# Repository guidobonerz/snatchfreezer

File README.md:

# SnatchFreezer (Beta)
SnatchFreezer is a project for Highspeed photography

Runs on Windows, Mac and Linux

This project also contains all required software and PCB layouts including:
- JavaFX - Controller Frontend
- Arduino Sketch
- Eagle PCB

Current Features:
- Connect up to six 12V driven valves or similar devices directly with 5 timing entries each.
- Connect up to two camera and/or flashes.

- Load and Save your settings
- Test all channels separately or altogether for 100ms.
- Toggle flushing all or single siphons from UI.
- Set amount of cycle loops
- Set delay time after each cycle loop.
- Describe each channel and/or the whole project
- Presets for TaT and Crown
- View log protocol
- Minimum valve delay/release time combination: 0,015 s -> 15 ms -> 15000 us / 0,004 s -> 4 ms -> 4000 us

Known Bugs:
- Data transfer sometimes hangs

Future plans:
- WLAN and/or Bluetooth Module
- Rest Api
- Android Client

# Build Java Application
mvn jfx:jar

# Download latest Frontend
[Snathfreezer Frontend](https://github.com/guidobonerz/snatchfreezer/blob/develop/download/snatchfreezer.zip)

## Shot 1

## Shot 2

## Controller View

## PCB

## Frame

## Siphons

## Valves

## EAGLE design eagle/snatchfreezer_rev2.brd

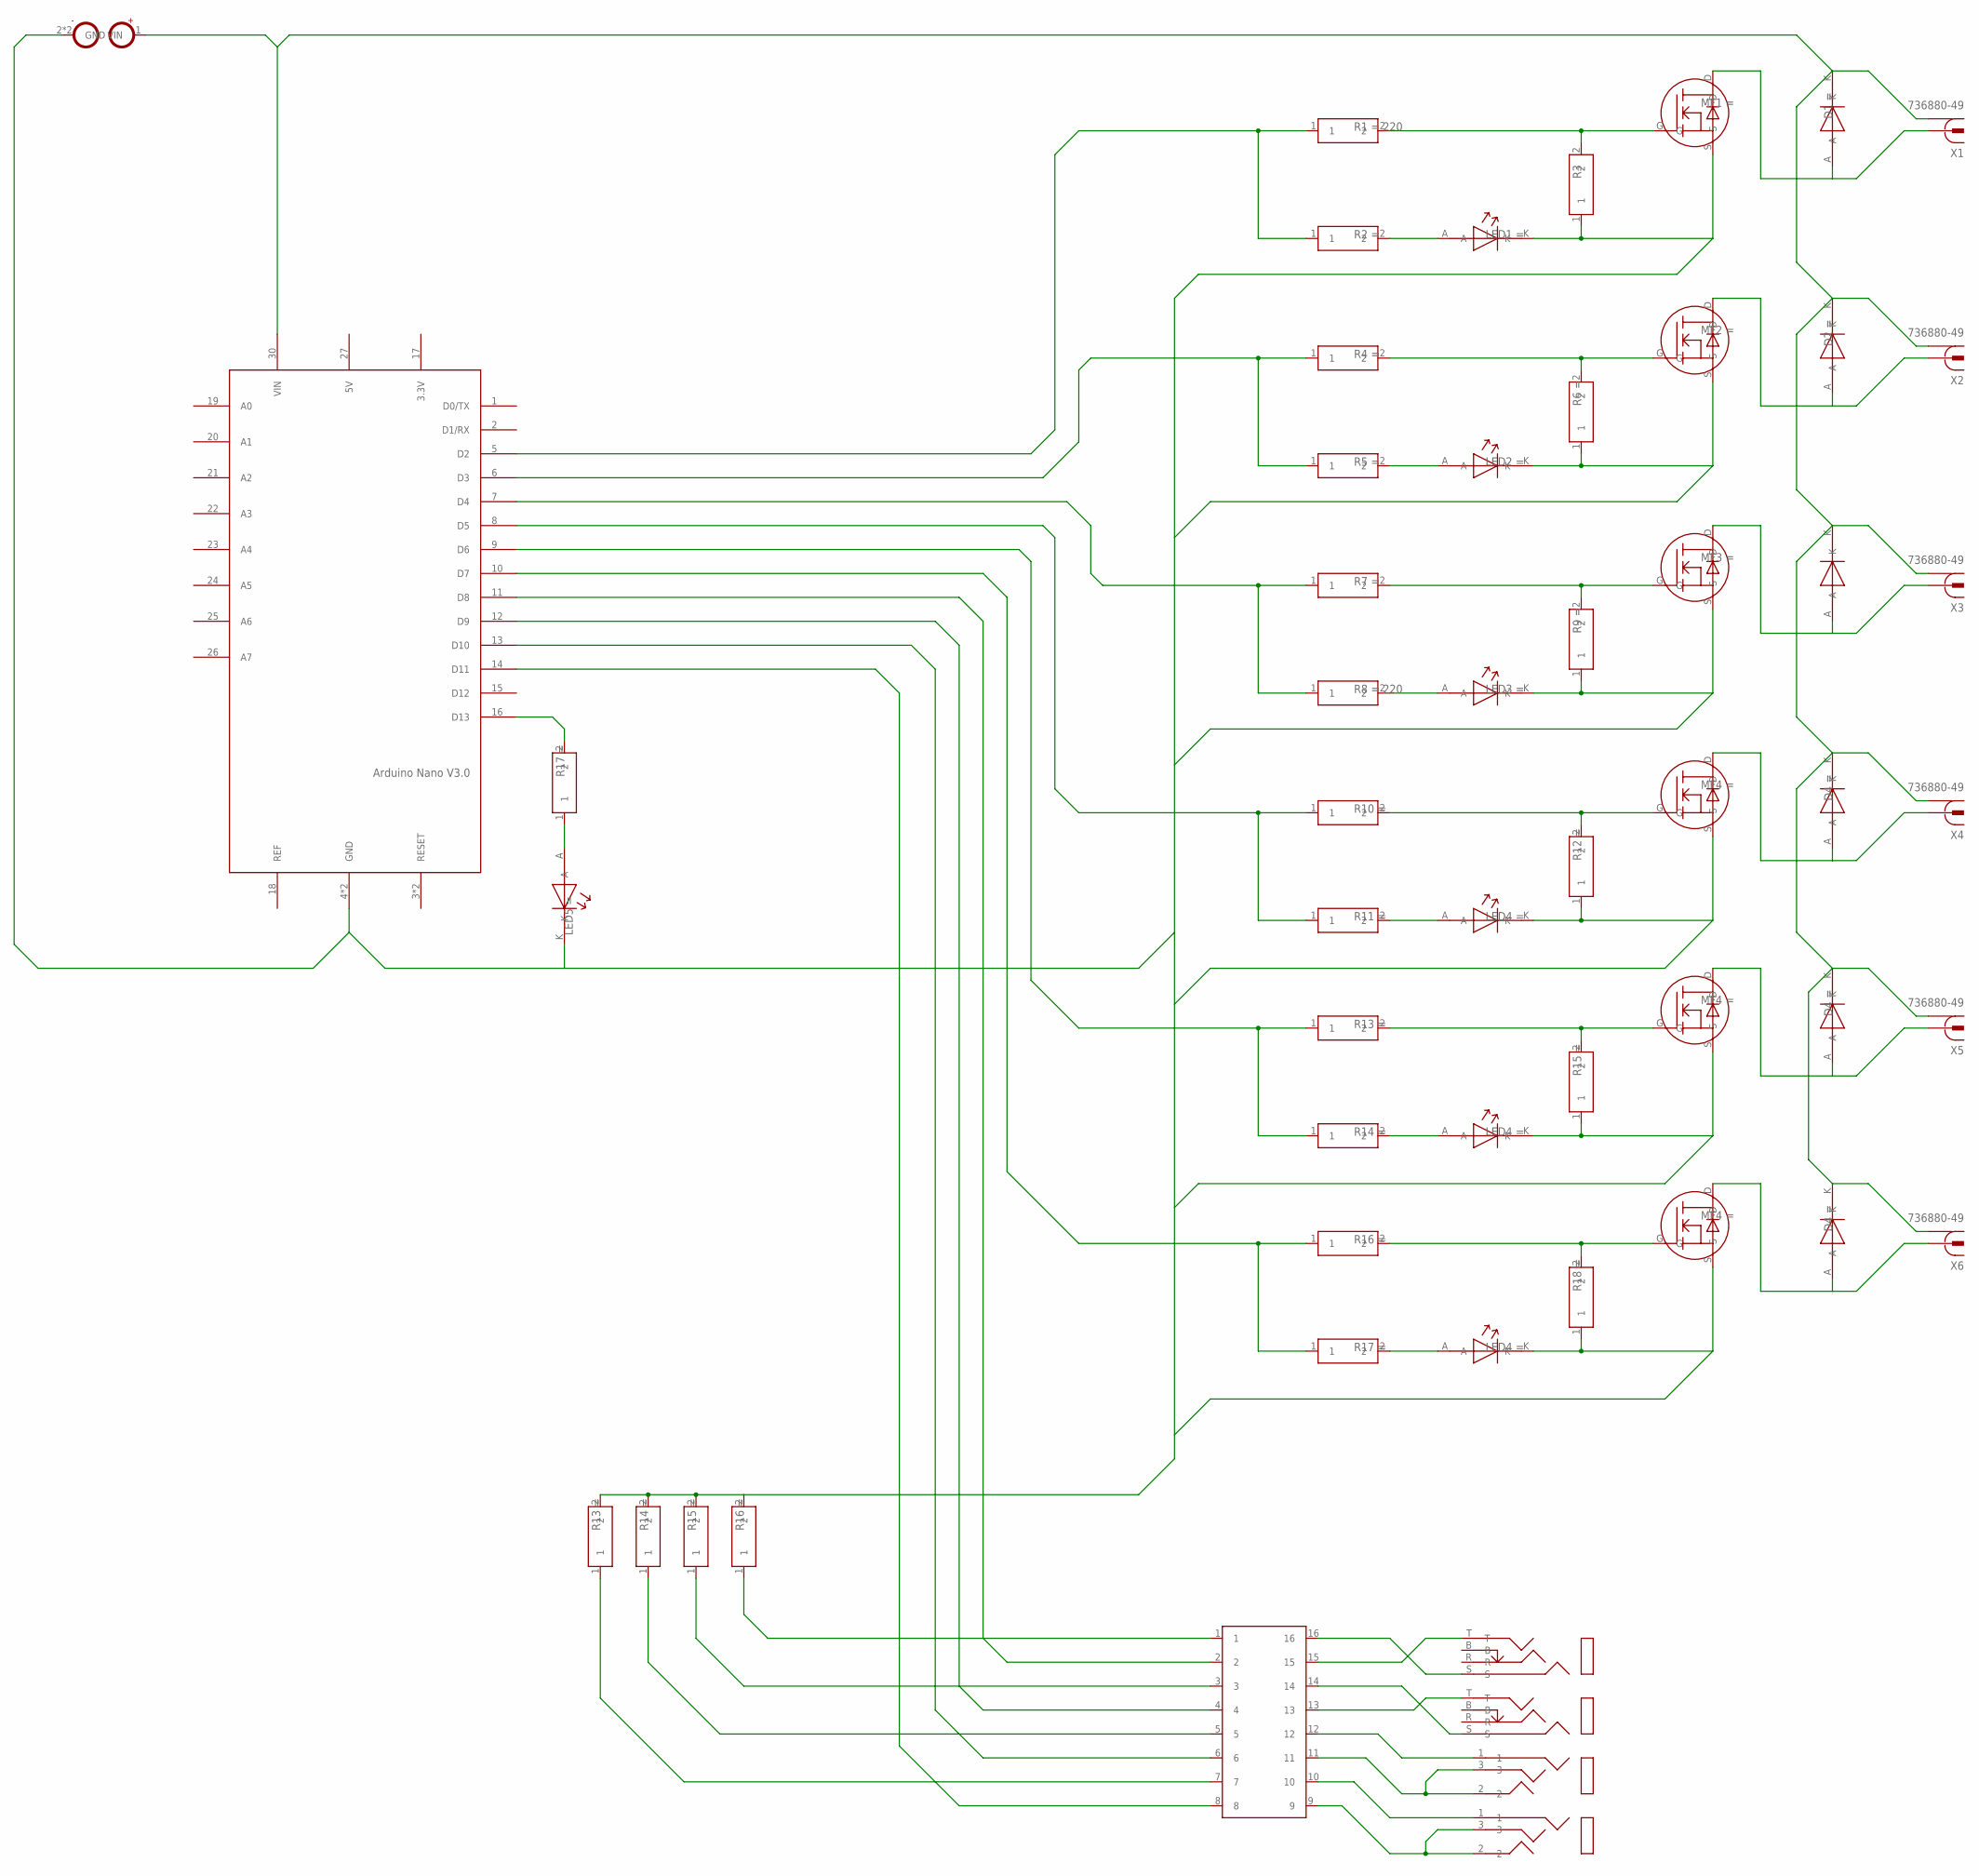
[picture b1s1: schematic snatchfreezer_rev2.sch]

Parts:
R1, R2, R3, R4, R5, R6, R7, R8, R9, R10, R11, R12, R13, R14, R15, R16, R17, R18: RESISTOR
U$1: ARDUINO_NANO30
U$2, U$3, U$4, U$16, U$20, U$28: IRLR8721
U$5, U$10, U$11, U$17, U$22, U$23, U$31: LED3MM
U$6, U$7: PHONEJACK_35
U$8: IC-16
U$9, U$30, U$37, U$38, U$39: RESISTOR
U$12, U$13, U$14, U$21, U$24, U$32: DIODE
U$36: POWER_CONNECT
U$40, U$41: PHONEJACK_25
X1, X2, X3, X4, X5, X6: 736880-49

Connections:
12V2: U$1.30 (VIN), U$12.K, U$13.K, U$14.K, U$21.K, U$24.K, U$32.K, U$36.1 (VIN), X1.GND (1), X2.GND (1), X3.GND (1), X4.GND (1), X5.GND (1), X6.GND (1)
GND2: R3.1, R6.1, R9.1, R12.1, R15.1, R18.1, U$1.4 (GND), U$1.29 (GND), U$2.S, U$3.S, U$4.S, U$5.K, U$10.K, U$11.K, U$16.S, U$17.K, U$20.S, U$22.K, U$23.K, U$28.S, U$30.2, U$31.K, U$36.2 (GND), U$36.3 (GND), U$37.2, U$38.2, U$39.2
unnamed: R1.2, R3.2, U$2.G
unnamed: U$2.D, U$12.A, X1.SIGNAL (2)
unnamed: R2.2, U$11.A
unnamed: U$7.S, U$8.16
unnamed: U$8.1, U$30.1
unnamed: R1.1, R2.1, U$1.5 (D2)
unnamed: U$3.D, U$13.A, X2.SIGNAL (2)
unnamed: U$8.3, U$37.1
unnamed: U$7.T, U$8.15
unnamed: R5.2, U$10.A
unnamed: R4.2, R6.2, U$3.G
unnamed: R4.1, R5.1, U$1.6 (D3)
unnamed: U$20.D, U$24.A, X3.SIGNAL (2)
unnamed: U$8.5, U$38.1
unnamed: U$8.7, U$39.1
unnamed: R8.2, U$23.A
unnamed: R7.2, R9.2, U$20.G
unnamed: R7.1, R8.1, U$1.7 (D4)
unnamed: U$28.D, U$32.A, X4.SIGNAL (2)
unnamed: U$1.11 (D8), U$8.2
unnamed: U$1.12 (D9), U$8.4
unnamed: R11.2, U$31.A
unnamed: R10.2, R12.2, U$28.G
unnamed: R10.1, R11.1, U$1.8 (D5)
unnamed: U$1.13 (D10), U$8.6
unnamed: U$1.14 (D11), U$8.8
unnamed: U$6.T, U$8.13
unnamed: U$6.S, U$8.14
unnamed: U$4.D, U$14.A, X5.SIGNAL (2)
unnamed: R14.2, U$5.A
unnamed: U$8.12, U$40.1
unnamed: U$8.11, U$40.2, U$40.3
unnamed: U$8.10, U$41.1
unnamed: U$8.9, U$41.2, U$41.3
unnamed: U$1.16 (D13), U$9.2
unnamed: U$9.1, U$22.A
unnamed: R13.2, R15.2, U$4.G
unnamed: R13.1, R14.1, U$1.9 (D6)
unnamed: U$16.D, U$21.A, X6.SIGNAL (2)
unnamed: R17.2, U$17.A
unnamed: R16.2, R18.2, U$16.G
unnamed: R16.1, R17.1, U$1.10 (D7)

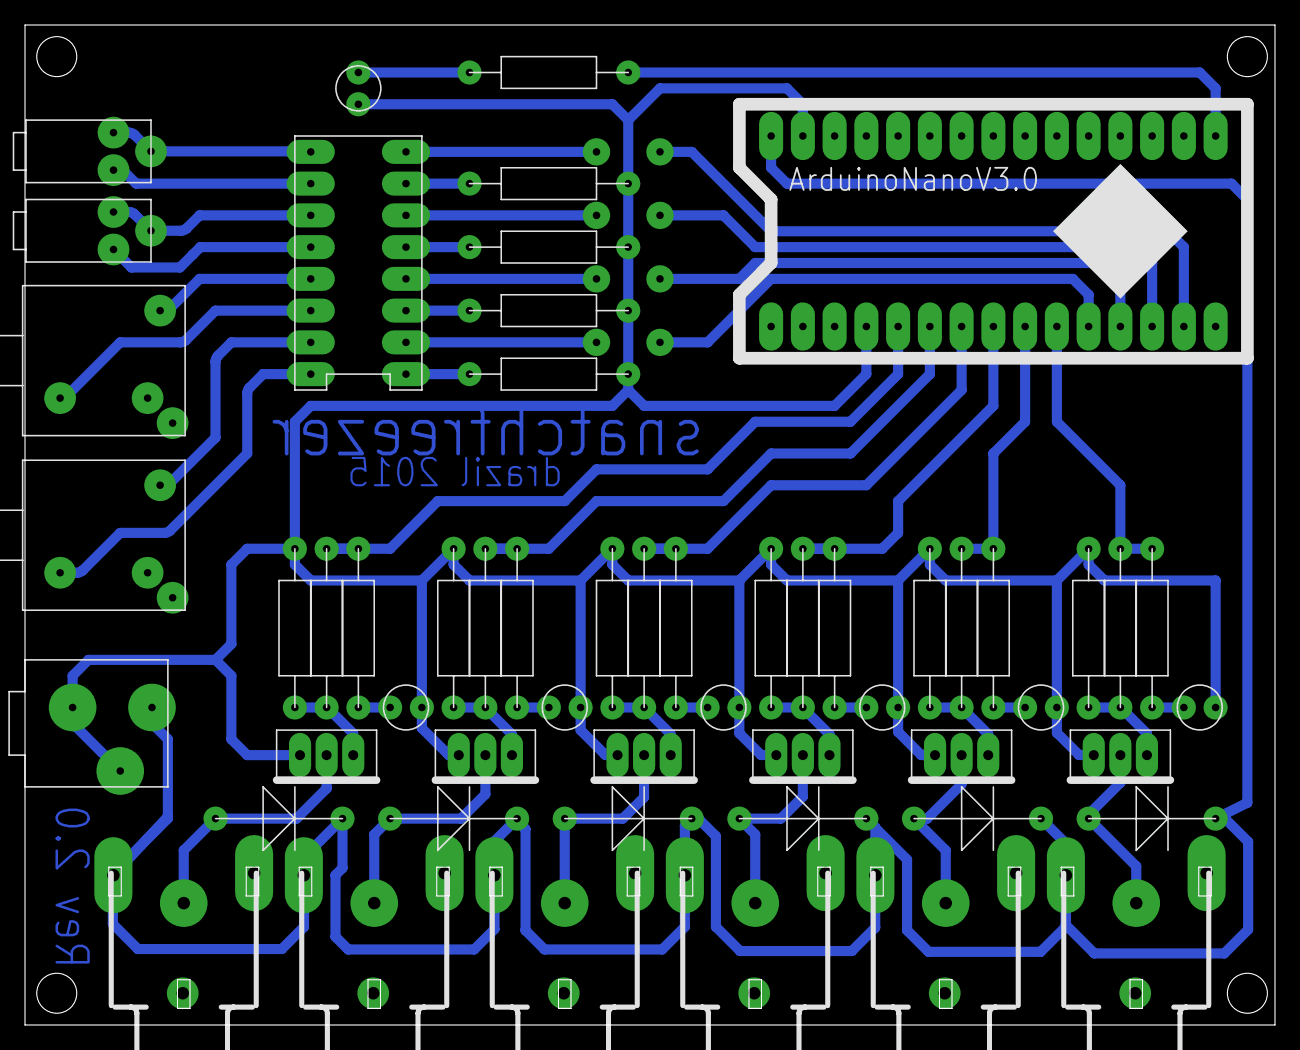
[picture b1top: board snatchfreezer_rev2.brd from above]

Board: 2 copper layers, 100.0 x 80.0 mm, 55 parts (0 on the bottom side), 44 nets.

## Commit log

2019-02-01 arduino/eagle
2019-02-25 update logger
2019-02-26 update serial protocol
2019-02-27 timing fix
2019-03-05 new frontend
2019-03-09 update styles
2019-03-10 update layout
2019-03-13 updates : multi language support
2019-03-13 lombok update
2019-03-13 layout update
2019-03-15 save/load settings
2019-03-15 added flush and test function
2019-03-15 code cleanup
2019-03-16 more cleanup
2019-03-16 update screenshot
2019-03-16 progress indicator
2019-03-16 update : screenshot
2019-03-29 downloadable frontend
2019-07-20 add error message and dialog
2019-11-13 Bump jackson-databind from 2.9.8 to 2.9.10.1 in /SnatchFreezer
    Bumps [jackson-databind](https://github.com/FasterXML/jackson) from 2.9.8 to 2.9.10.1.
    - [Release notes](https://github.com/FasterXML/jackson/releases)
    - [Commits](https://github.com/FasterXML/jackson/commits)
2020-03-04 Bump jackson-databind from 2.9.8 to 2.9.10.3 in /SnatchFreezer
    Bumps [jackson-databind](https://github.com/FasterXML/jackson) from 2.9.8 to 2.9.10.3.
    - [Release notes](https://github.com/FasterXML/jackson/releases)
    - [Commits](https://github.com/FasterXML/jackson/commits)
2020-03-26 update dependencies
2020-04-23 Bump jackson-databind from 2.9.8 to 2.9.10.4 in /SnatchFreezer
    Bumps [jackson-databind](https://github.com/FasterXML/jackson) from 2.9.8 to 2.9.10.4.
    - [Release notes](https://github.com/FasterXML/jackson/releases)
    - [Commits](https://github.com/FasterXML/jackson/commits)
2020-05-07 add snapshots
2021-02-18 Bump jackson-databind from 2.10.3 to 2.10.5.1 in /SnatchFreezer
    Bumps [jackson-databind](https://github.com/FasterXML/jackson) from 2.10.3 to 2.10.5.1.
    - [Release notes](https://github.com/FasterXML/jackson/releases)
    - [Commits](https://github.com/FasterXML/jackson/commits)
2022-10-05 Bump jackson-databind from 2.10.3 to 2.12.6.1 in /SnatchFreezer
    Bumps [jackson-databind](https://github.com/FasterXML/jackson) from 2.10.3 to 2.12.6.1.
    - [Release notes](https://github.com/FasterXML/jackson/releases)
    - [Commits](https://github.com/FasterXML/jackson/commits)
    ---
    updated-dependencies:
    - dependency-name: com.fasterxml.jackson.core:jackson-databind
2022-10-18 Bump jackson-databind from 2.10.3 to 2.13.4.1 in /SnatchFreezer
    Bumps [jackson-databind](https://github.com/FasterXML/jackson) from 2.10.3 to 2.13.4.1.
    - [Release notes](https://github.com/FasterXML/jackson/releases)
    - [Commits](https://github.com/FasterXML/jackson/commits)
    ---
    updated-dependencies:
    - dependency-name: com.fasterxml.jackson.core:jackson-databind
2022-11-16 Bump jackson-databind from 2.10.3 to 2.12.7.1 in /SnatchFreezer
    Bumps [jackson-databind](https://github.com/FasterXML/jackson) from 2.10.3 to 2.12.7.1.
    - [Release notes](https://github.com/FasterXML/jackson/releases)
    - [Commits](https://github.com/FasterXML/jackson/commits)
    ---
    updated-dependencies:
    - dependency-name: com.fasterxml.jackson.core:jackson-databind
